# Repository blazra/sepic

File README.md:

# SEPIC
SEPIC converter design as a school project

Schematic: [kicad/sepic/sepic.pdf](kicad/sepic/sepic.pdf)  
Write-up in czech: [SEPIC_Radovan_Blazek.pdf](SEPIC_Radovan_Blazek.pdf)  
LibreOffice sheet with measured data: [Measurements.ods](Measurements.ods)  
LibreOffice sheet with component values calculations as per LT8710 datasheet: [SEPIC_calculations.ods](SEPIC_calculations.ods)  
LT8710 datasheet: https://www.analog.com/media/en/technical-documentation/data-sheets/8710f.pdf

Bugs in Rev. 1:
- SYNC input of the LT8710 is not pulled to GND

3D render: 

Photo of the finished board:

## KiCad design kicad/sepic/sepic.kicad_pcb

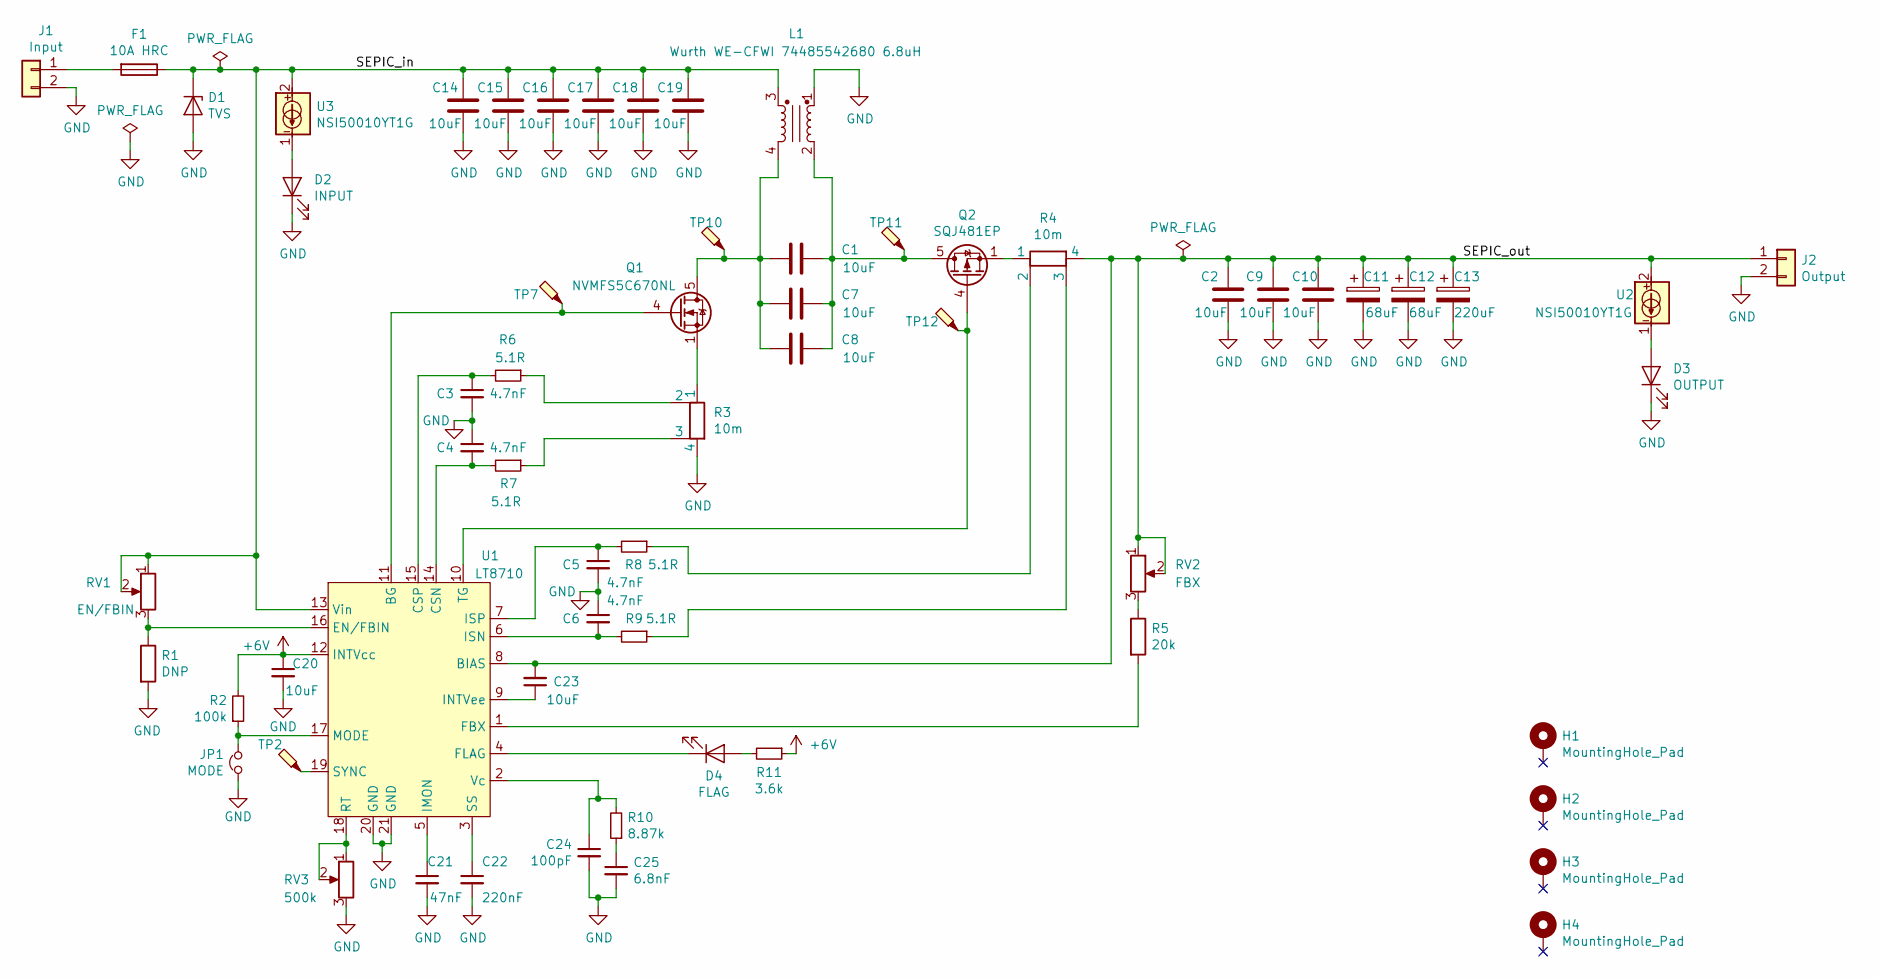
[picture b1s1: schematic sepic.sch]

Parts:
C1, C2, C7, C8, C9, C10, C14, C15, C16, C17, C18, C19: 10uF; C_1206_3216Metric
C3, C4, C5, C6: 4.7nF; C_0805_2012Metric
C11, C12: 68uF; CP_Elec_10x12.5
C13: 220uF; CP_Elec_10x12.5
C20, C23: 10uF; C_0805_2012Metric
C21: 47nF; C_0805_2012Metric
C22: 220nF; C_0805_2012Metric
C24: 100pF; C_0805_2012Metric
C25: 6.8nF; C_0805_2012Metric
D1: TVS; D_SMC
D2: INPUT; LED_0805_2012Metric_Castellated
D3: OUTPUT; LED_0805_2012Metric_Castellated
D4: FLAG; LED_0805_2012Metric_Castellated
F1: 10A HRC; Fuseholder_Cylinder-5x20mm_Schurter_OGN-SMD_Horizontal_Open
H1, H2, H3, H4: MountingHole_Pad; MountingHole_3.2mm_M3_Pad
J1: Input; TerminalBlock_PTR_P5.00mm_Horizontal
J2: Output; TerminalBlock_PTR_P5.00mm_Horizontal
JP1: MODE; PinHeader_1x02_P2.54mm_Vertical
L1: Wurth WE-CFWI 74485542680 6.8uH; Wurth_WE-CFWI_1813
Q1: NVMFS5C670NL; TDSON-8-1
Q2: SQJ481EP; TDSON-8-1
R1: DNP; R_0805_2012Metric
R2: 100k; R_0805_2012Metric
R3, R4: 10m; R_2512_6332Metric
R5: 20k; R_0805_2012Metric
R6, R7, R8, R9: 5.1R; R_0805_2012Metric
R10: 8.87k; R_0805_2012Metric
R11: 3.6k; R_0805_2012Metric
RV1: EN/FBIN; Potentiometer_Vishay_TS53YJ_Vertical
RV2: FBX; Potentiometer_Bourns_3296W_Vertical
RV3: 500k; Potentiometer_Vishay_TS53YJ_Vertical
TP2, TP7, TP10, TP11, TP12: TEST_POINT; TestPoint_Pad_D1.0mm
U1: LT8710; HTSSOP-20-1EP_4.4x6.5mm_P0.65mm_EP3.4x6.5mm_Mask2.75x3.43mm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
U2, U3: NSI50010YT1G; D_SOD-123

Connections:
+6V: C20.1, R2.2, R11.1, U1.12 (INTVcc)
/SEPIC_in: C14.2, C15.2, C16.2, C17.2, C18.2, C19.2, D1.1 (K), F1.1, L1.3, RV1.1, RV1.2, U1.13 (Vin), U3.2
/SEPIC_out: C2.1, C9.1, C10.1, C11.1, C12.1, C13.1, C23.2, J2.1, R4.4, RV2.1, RV2.2, U1.8 (BIAS), U2.2
GND: C2.2, C3.2, C4.1, C5.2, C6.1, C9.2, C10.2, C11.2, C12.2, C13.2, C14.1, C15.1, C16.1, C17.1, C18.1, C19.1, C20.2, C21.2, C22.2, C24.2, C25.2, D1.2 (A), D2.1 (K), D3.1 (K), J1.2, J2.2, JP1.1, L1.1, R1.2, R3.4, RV3.3, U1.20 (GND), U1.21 (GND)
unnamed: C1.1, C7.1, C8.1, L1.2, Q2.5 (D), TP11.1
unnamed: C1.2, C7.2, C8.2, L1.4, Q1.5 (D), TP10.1
unnamed: C3.1, R6.2, U1.15 (CSP)
unnamed: C4.2, R7.2, U1.14 (CSN)
unnamed: C5.1, R8.2, U1.7 (ISP)
unnamed: C6.2, R9.2, U1.6 (ISN)
unnamed: C21.1, U1.5 (IMON)
unnamed: C22.1, U1.3 (SS)
unnamed: C23.1, U1.9 (INTVee)
unnamed: C24.1, R10.2, U1.2 (Vc)
unnamed: C25.1, R10.1
unnamed: D2.2 (A), U3.1
unnamed: D3.2 (A), U2.1
unnamed: D4.1 (K), U1.4 (FLAG)
unnamed: D4.2 (A), R11.2
unnamed: F1.2, J1.1
unnamed: JP1.2, R2.1, U1.17 (MODE)
unnamed: Q1.1 (S), Q1.2 (S), Q1.3 (S), R3.1
unnamed: Q1.4 (G), TP7.1, U1.11 (BG)
unnamed: Q2.1 (S), Q2.2 (S), Q2.3 (S), R4.1
unnamed: Q2.4 (G), TP12.1, U1.10 (TG)
unnamed: R1.1, RV1.3, U1.16 (EN/FBIN)
unnamed: R5.1, RV2.3
unnamed: R5.2, U1.1 (FBX)
unnamed: R3.2, R6.1
unnamed: R3.3, R7.1
unnamed: R4.2, R8.1
unnamed: R4.3, R9.1
unnamed: RV3.1, RV3.2, U1.18 (RT)
unnamed: TP2.1, U1.19 (SYNC)

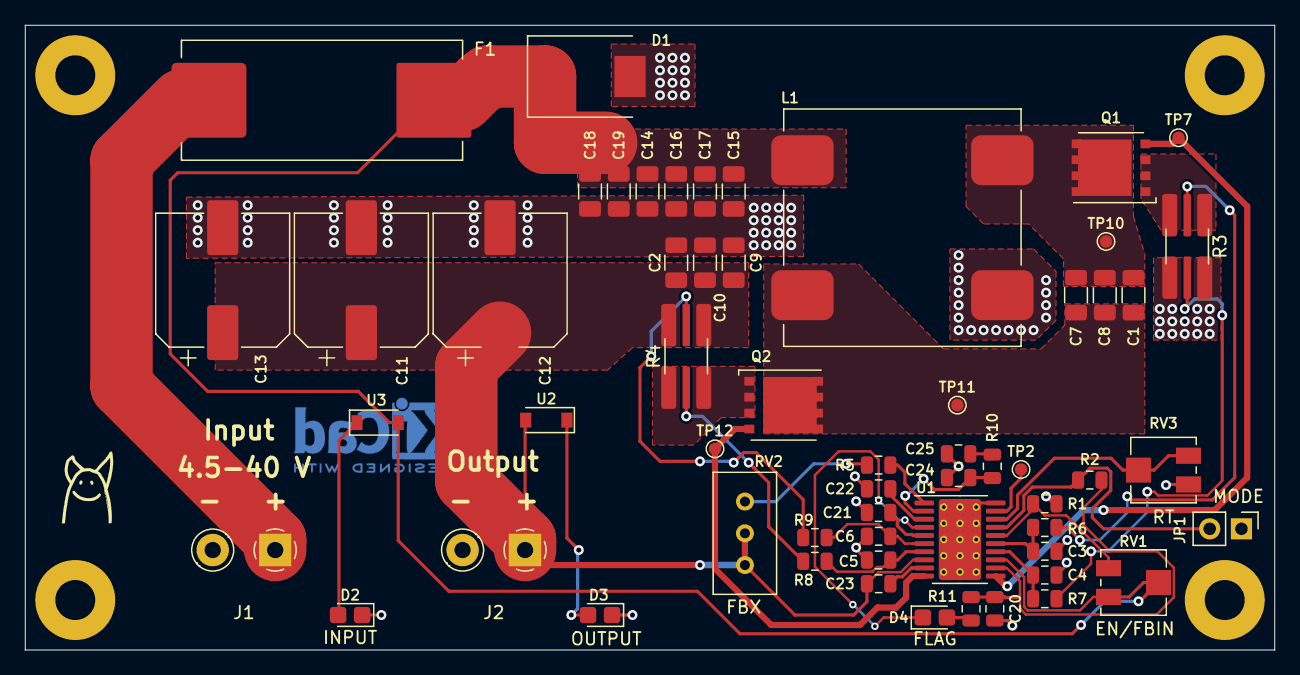
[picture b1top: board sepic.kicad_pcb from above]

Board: 2 copper layers, 100.0 x 50.0 mm, 62 parts (0 on the bottom side), 34 nets.

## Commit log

2019-06-16 Add pdf with czech write-up
